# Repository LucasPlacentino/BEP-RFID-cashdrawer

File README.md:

# BEP-RFID-cashdrawer
 rfid cashdrawer arduino controller pcb

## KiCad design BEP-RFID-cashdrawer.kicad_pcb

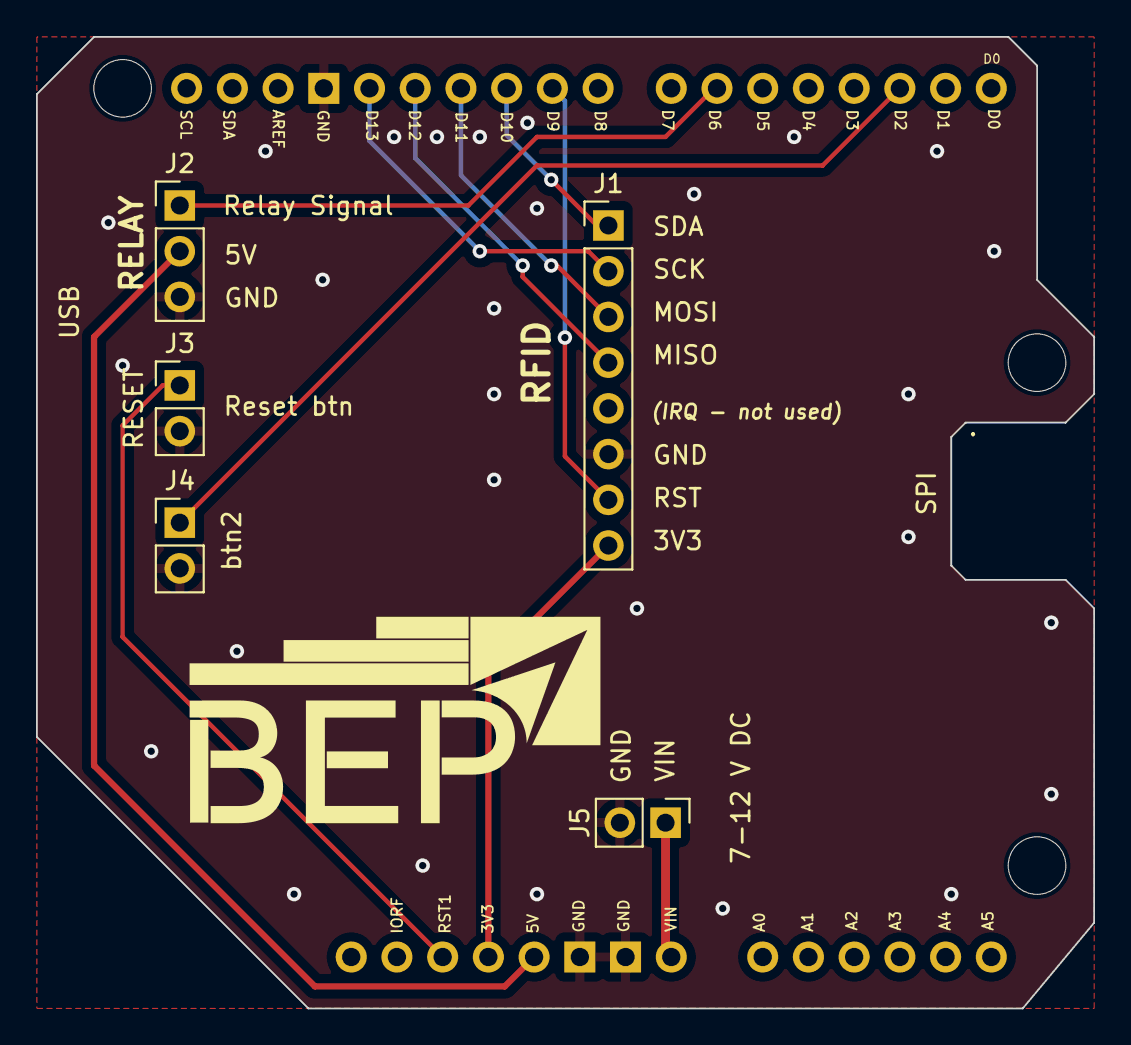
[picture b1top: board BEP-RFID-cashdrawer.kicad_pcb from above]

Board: 2 copper layers, 58.7 x 54.0 mm, 6 parts (0 on the bottom side), 12 nets.

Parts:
J1: Conn_01x08; PinHeader_1x08_P2.54mm_Vertical
J2: Conn_01x03; PinHeader_1x03_P2.54mm_Vertical
J3, J4, J5: Conn_01x02; PinHeader_1x02_P2.54mm_Vertical
XA1: Arduino_Uno_R3_Shield

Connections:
+3.3V: J1.8, XA1.3V3 (3.3V)
+5V: J2.2, XA1.5V1 (5V)
Bypass: J4.1, XA1.D2 (D2_INT0)
GND: J1.6, J2.3, J3.2, J4.2, J5.2, XA1.GND1 (GND), XA1.GND2 (GND), XA1.GND3 (GND)
MISO: J1.4, XA1.D12
MOSI: J1.3, XA1.D11
POWERIN: J5.1, XA1.VIN
RST: J1.7, XA1.D9
Relay: J2.1, XA1.D6
Reset button: J3.1, XA1.RST1 (RESET)
SCK: J1.2, XA1.D13
SDA: J1.1, XA1.D10 (D10_CS)

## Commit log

2023-09-07 initial schematic
2023-09-08 update 2
